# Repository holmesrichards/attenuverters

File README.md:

# Attenuverters

This is a utility synthesizer module in Kosmo format. It provides three attenuverters — that is, on each of the Out 1/2/3 outputs is whatever voltage went into In 1/2/3 with buffering and attenuation and, if the attenuator slider is below the midpoint, inverted as well. 

A toggle switch allows replacing In 1 with a 10 volt reference, allowing you to get any DC voltage from -10 V to +10 V on Out 1.

The sum of the three outputs appears on the Sum Out jack, and the inverted sum on the inverted Sum Out jack.

The attenuverters' response to the slider position is nonlinear: it is steeper on the ends than in the middle, making it easier to set small values precisely.

The design is inspired and informed by the Kassutronics Attenuverter/Mixer Eurorack module.

## Current draw
11 mA +12 V, 10 mA -12 V

## Photos

## Documentation

* [Schematic](Docs/attenuverters.pdf)
* PCB layout: [front](Docs/attenuverters_layout_front.pdf), [back](Docs/attenuverters_layout_back.pdf)
* [BOM](Docs/attenuverters_bom.md)
* [Build notes](Docs/attenuverters_build.md)

## GitHub repository

* [https://github.com/holmesrichards/attenuverters](https://github.com/holmesrichards/attenuverters)

## Submodules

This repo uses submodules aoKicad and Kosmo_panel, which provide needed libaries for KiCad. To clone:

```
git clone git@github.com:holmesrichards/attenuverters.git
git submodule init
git submodule update
```

Alternatively do

```
git clone --recurse-submodules git@github.com:holmesrichards/attenuverters.git
```

Or if you download the repository as a zip file, you must also click on the "aoKicad" and "Kosmo\_panel" links on the GitHub page (they'll have "@ something" after them) and download them as separate zip files which you can unzip into this repo's aoKicad and Kosmo\_panel directories.

If desired, copy the files from aoKicad and Kosmo\_panel to wherever you prefer (your KiCad user library directory, for instance, if you have one). Then in KiCad, go into Edit Symbols and add symbol libraries 

```
aoKicad/ao_symbols
Kosmo_panel/Kosmo
```
and go into Edit Footprints and add footprint libraries 
```
aoKicad/ao_tht
Kosmo_panel/Kosmo_panel.
```

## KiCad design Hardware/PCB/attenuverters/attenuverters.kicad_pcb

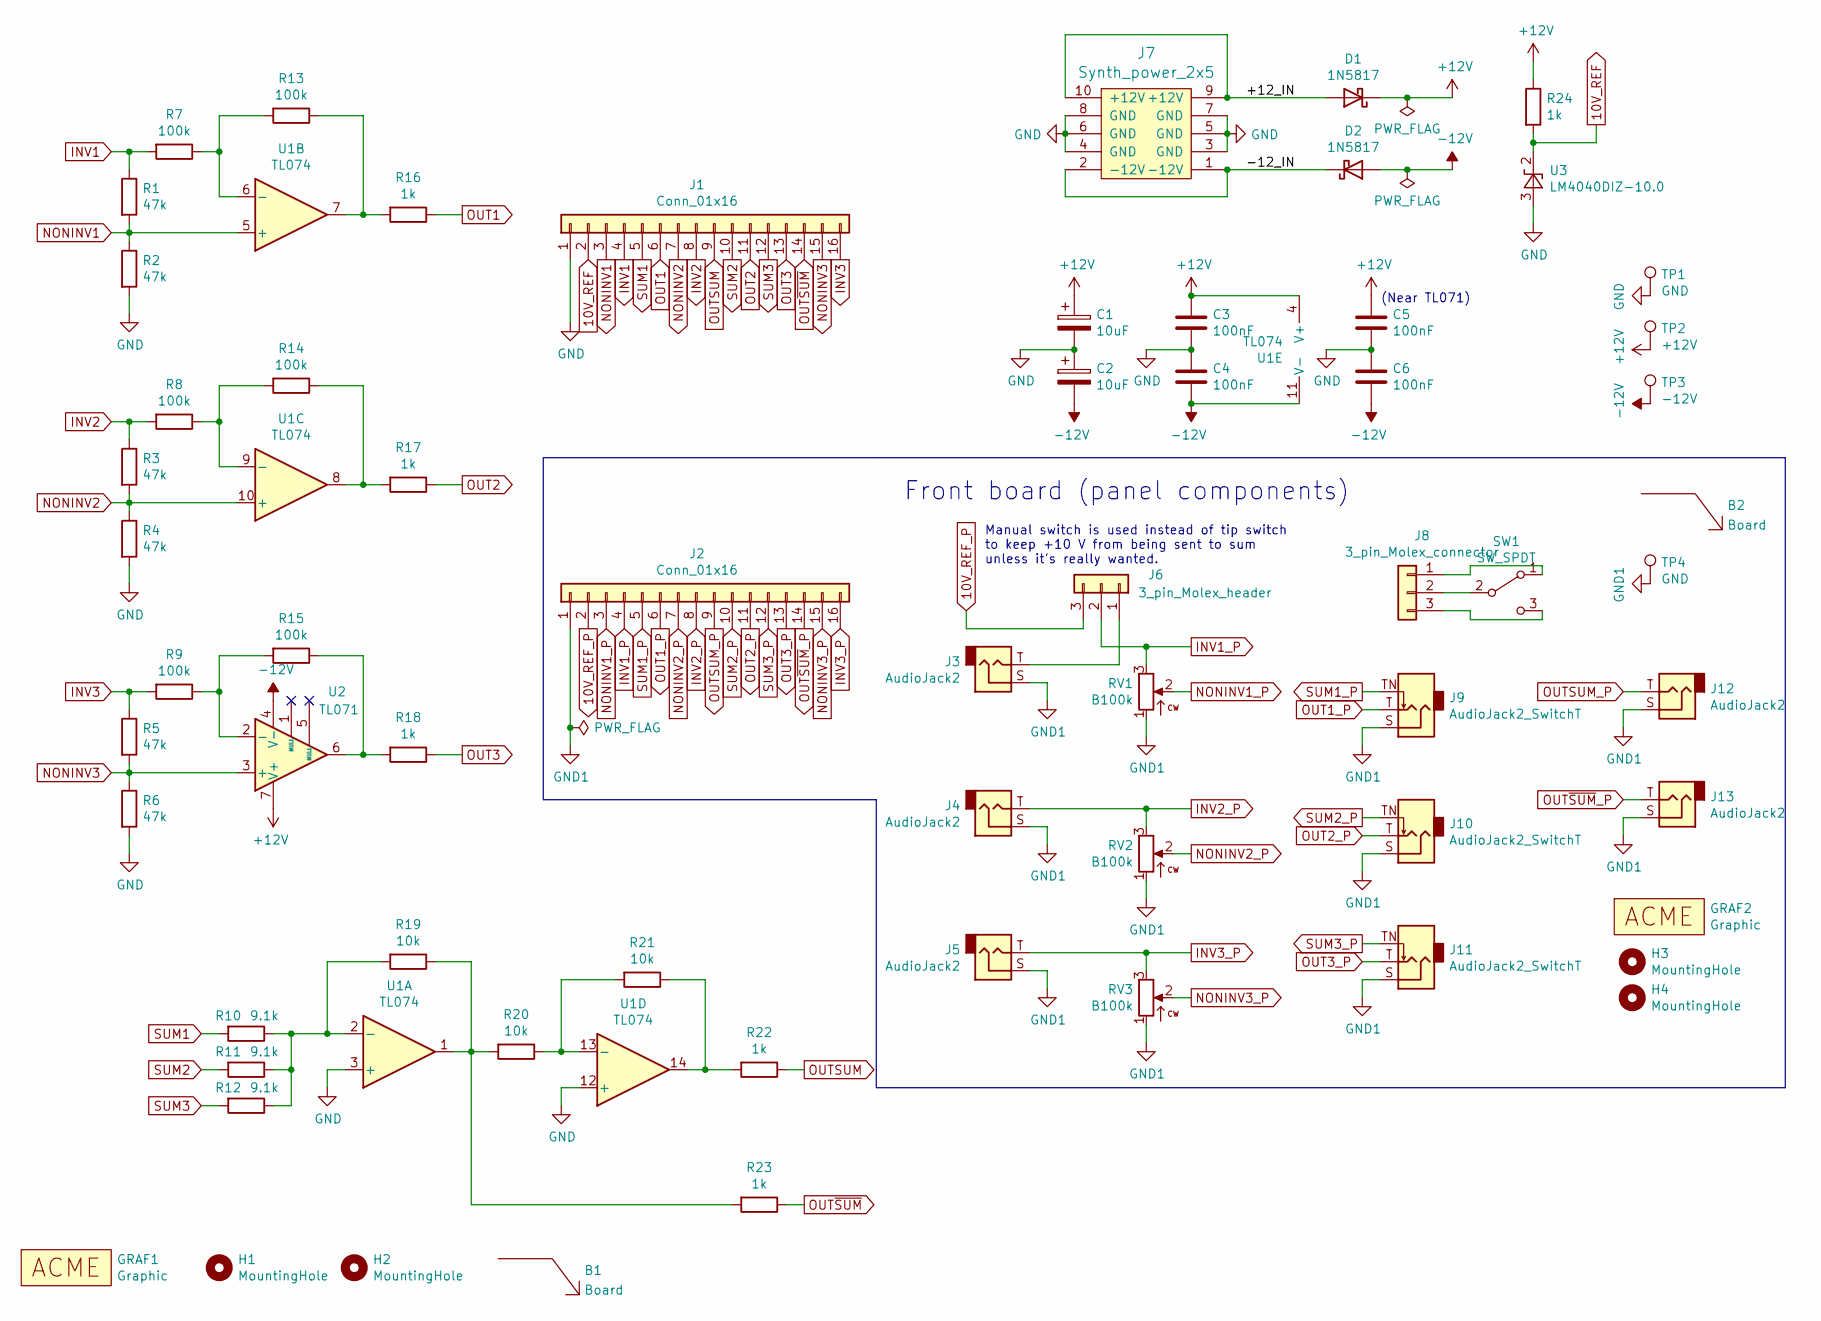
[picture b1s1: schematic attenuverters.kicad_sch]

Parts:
B1, B2: Board; Board_Marker
C1, C2: 10uF; CP_Radial_D6.3mm_P2.50mm
C3, C4, C5, C6: 100nF; C_Disc_D3.0mm_W1.6mm_P2.50mm
D1, D2: 1N5817; D_DO-41_SOD81_P10.16mm_Horizontal
GRAF1: Graphic; attenuverters_panel_holes
GRAF2: Graphic; analogoutput_12mm
H1, H2, H3, H4: MountingHole; MountingHole_3.2mm_M3
J1: Conn_01x16; PinHeader_1x16_P2.54mm_Vertical
J2: Conn_01x16; PinSocket_1x16_P2.54mm_Vertical
J3, J4, J5, J12, J13: AudioJack2
J6: 3_pin_Molex_header; Molex_KK-254_AE-6410-03A_1x03_P2.54mm_Vertical
J7: Synth_power_2x5; Power_Header
J8: 3_pin_Molex_connector; Molex_KK-254_AE-6410-03A_1x03_P2.54mm_Vertical
J9, J10, J11: AudioJack2_SwitchT
R1, R2, R3, R4, R5, R6: 47k; R_Axial_DIN0207_L6.3mm_D2.5mm_P10.16mm_Horizontal
R7, R8, R9, R13, R14, R15: 100k; R_Axial_DIN0207_L6.3mm_D2.5mm_P10.16mm_Horizontal
R10, R11, R12: 9.1k; R_Axial_DIN0207_L6.3mm_D2.5mm_P10.16mm_Horizontal
R16, R17, R18, R22, R23, R24: 1k; R_Axial_DIN0207_L6.3mm_D2.5mm_P10.16mm_Horizontal
R19, R20, R21: 10k; R_Axial_DIN0207_L6.3mm_D2.5mm_P10.16mm_Horizontal
RV1, RV2, RV3: B100k; Potentiometer_Alpha_RA6020F_Single_Slide
SW1: SW_SPDT; SPDT-toggle-switch-1M-series
TP1, TP4: GND; TestPoint_THTPad_1.5x1.5mm_Drill0.7mm
TP2: +12V; TestPoint_THTPad_D1.5mm_Drill0.7mm
TP3: -12V; TestPoint_THTPad_D1.5mm_Drill0.7mm
U1: TL074; DIP-14_W7.62mm_Socket_LongPads
U2: TL071; DIP-8_W7.62mm_Socket_LongPads
U3: LM4040DIZ-10.0; TO-92_Inline_Wide

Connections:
10V_REF: J1.2, R24.2, U3.2 (K)
10V_REF_P: J2.2, J6.3
+12V: C1.1, C3.1, C5.1, D1.1 (K), R24.1, TP2.1, U1.4 (V+), U2.7 (V+)
-12V: C2.2, C4.2, C6.2, D2.2 (A), TP3.1, U1.11 (V-), U2.4 (V-)
/+12_IN: D1.2 (A), J7.9 (+12V), J7.10 (+12V)
/-12_IN: D2.1 (K), J7.1 (-12V), J7.2 (-12V)
GND: C1.2, C2.1, C3.2, C4.1, C5.2, C6.1, J1.1, J7.3 (GND), J7.4 (GND), J7.5 (GND), J7.6 (GND), J7.7 (GND), J7.8 (GND), R2.2, R4.2, R6.2, TP1.1, U1.3 (+), U1.12 (+), U3.3 (A)
GND1: J2.1, J3.S, J4.S, J5.S, J9.S, J10.S, J11.S, J12.S, J13.S, RV1.1, RV2.1, RV3.1, TP4.1
INV1: J1.4, R1.1, R7.2
INV1_P: J2.4, J6.2, RV1.3
INV2: J1.8, R3.1, R8.2
INV2_P: J2.8, J4.T, RV2.3
INV3: J1.16, R5.1, R9.2
INV3_P: J2.16, J5.T, RV3.3
NONINV1: J1.3, R1.2, R2.1, U1.5 (+)
NONINV1_P: J2.3, RV1.2
NONINV2: J1.7, R3.2, R4.1, U1.10 (+)
NONINV2_P: J2.7, RV2.2
NONINV3: J1.15, R5.2, R6.1, U2.3 (+)
NONINV3_P: J2.15, RV3.2
unnamed: J3.T, J6.1
unnamed: J8.1, SW1.1 (A)
unnamed: J8.2, SW1.2 (B)
unnamed: J8.3, SW1.3 (C)
unnamed: R10.1, R11.1, R12.1, R19.2, U1.2 (-)
unnamed: R13.1, R16.2, U1.7
unnamed: R7.1, R13.2, U1.6 (-)
unnamed: R14.1, R17.2, U1.8
unnamed: R8.1, R14.2, U1.9 (-)
unnamed: R15.1, R18.2, U2.6
unnamed: R9.1, R15.2, U2.2 (-)
unnamed: R19.1, R20.2, R23.2, U1.1
unnamed: R20.1, R21.2, U1.13 (-)
unnamed: R21.1, R22.2, U1.14
OUT1: J1.6, R16.1
OUT1_P: J2.6, J9.T
OUT2: J1.11, R17.1
OUT2_P: J2.11, J10.T
OUT3: J1.13, R18.1
OUT3_P: J2.13, J11.T
OUTSUM: J1.9, R22.1
OUTSUM_P: J2.9, J12.T
OUT~SUM: J1.14, R23.1
OUT~SUM_P: J2.14, J13.T
SUM1: J1.5, R10.2
SUM1_P: J2.5, J9.TN
SUM2: J1.10, R11.2
SUM2_P: J2.10, J10.TN
SUM3: J1.12, R12.2
SUM3_P: J2.12, J11.TN

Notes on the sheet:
(Near TL071)
Manual switch is used instead of tip switch to keep +10 V from being sent to sum unless it's really wanted.
Front board (panel components)

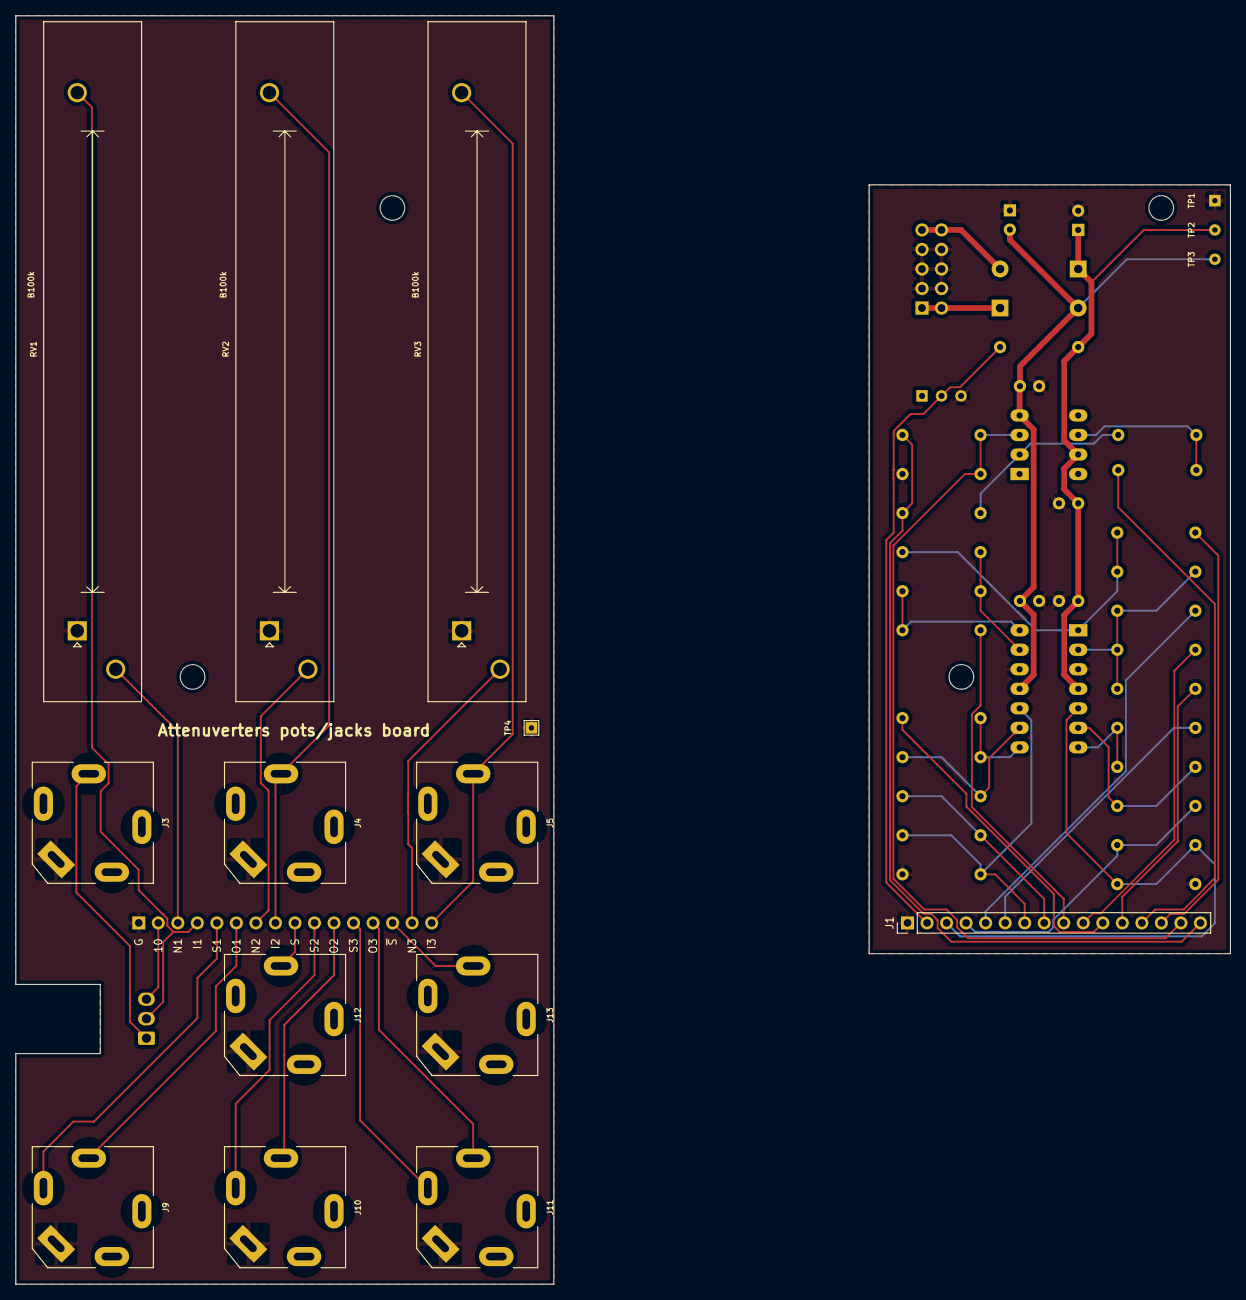
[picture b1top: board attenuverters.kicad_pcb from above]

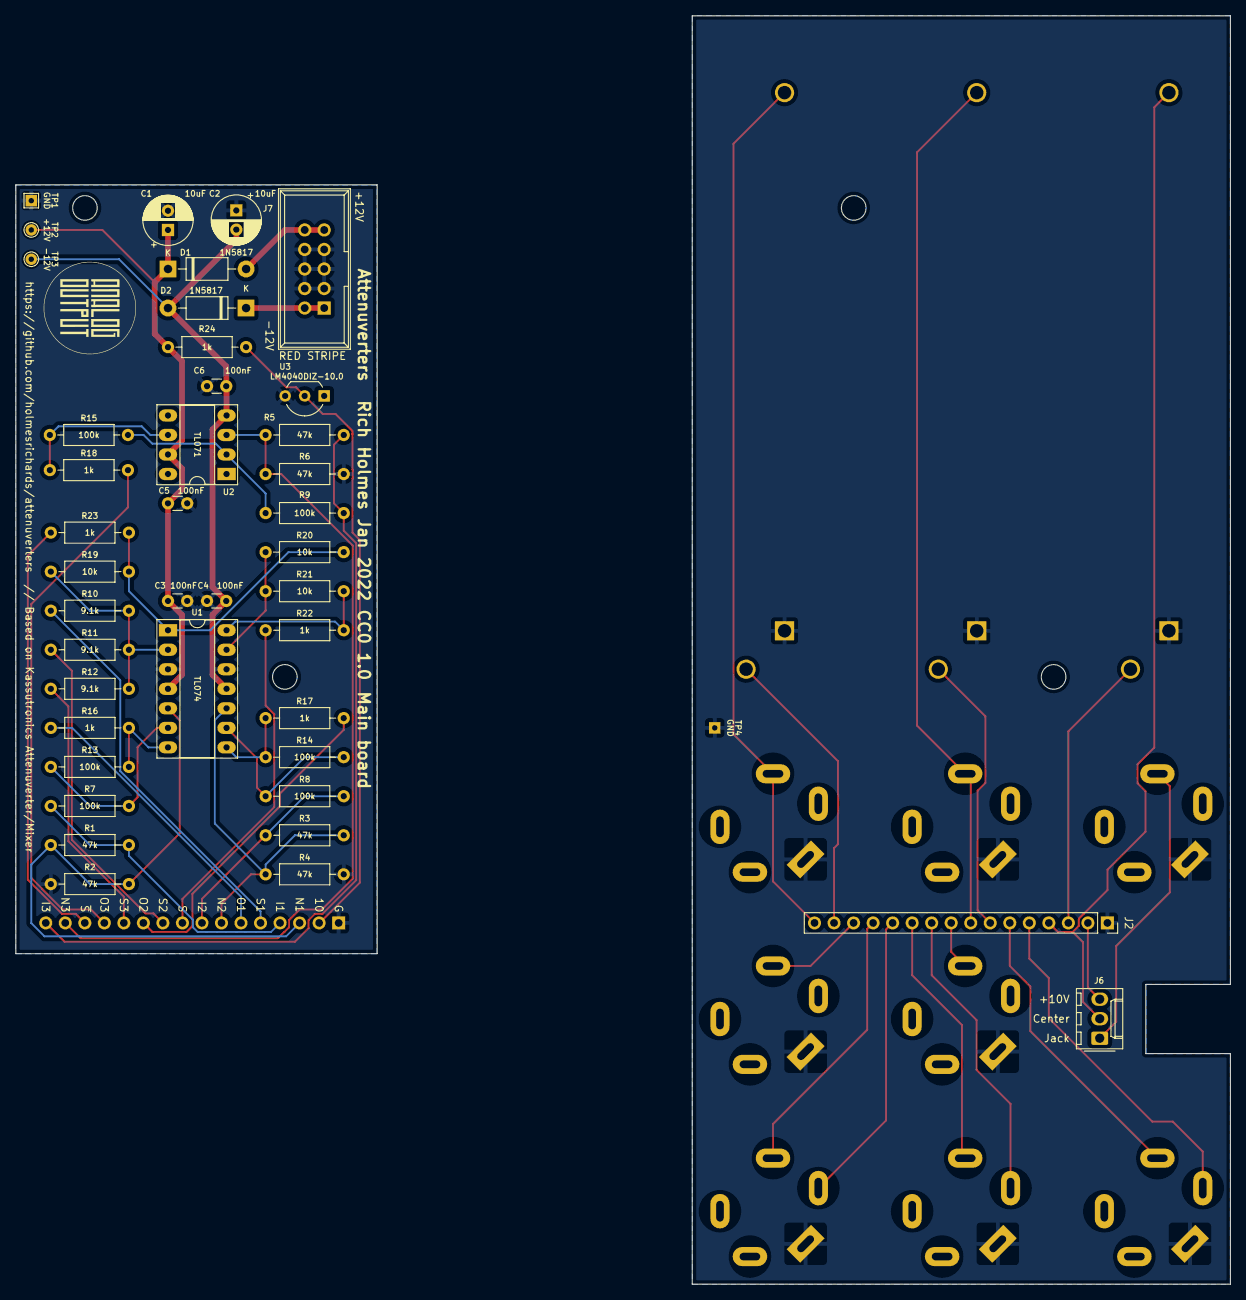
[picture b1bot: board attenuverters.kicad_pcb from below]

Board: 2 copper layers, 158.0 x 165.0 mm, 62 parts (42 on the bottom side), 47 nets.

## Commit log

2021-10-15 Initial version
2021-10-19 +10V_P symbol in new local library
2021-10-31 k not K; BOM
2021-11-01 Revised PCB
2021-11-01 Panel in KiCad
2021-11-02 Rear panel labels
2021-11-12 2x072->074, correct wrong power connections
2021-11-18 Test points
2021-12-05 README edit; panel art
2021-12-25 README
2022-02-01 Better .gitignore; KiCad 6 version
2022-03-27 Catch up to 1st fab run version
2022-03-27 Create LICENSE
2022-03-27 Slot version of jacks
2022-03-27 Typo; specify 1/4" jacks

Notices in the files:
Hardware/PCB/attenuverters/attenuverters.kicad_pcb:
Rich Holmes Jan 2022 CC0 1.0
